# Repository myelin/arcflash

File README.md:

# Arcflash

A board that plugs into all Acorn Archimedes, A3000, A5000 (with adapter), and
Risc PC (with adapter) machines, allowing OS updates without opening the
machine -- or even powering it down!

[Detailed design info](DESIGN.md)

[Stardot thread](https://stardot.org.uk/forums/viewtopic.php?f=16&t=16043)

Pictures
--------

Assembly notes
--------------

For IC sockets, cut two 40-pin headers to make:

- one 2x16-pin header and one 2x4-pin headers
- four 5+4-pin headers and two 2-pin headers

Note from my employer
---------------------

This is not an officially supported Google product. This project is not
eligible for the [Google Open Source Software Vulnerability Rewards
Program](https://bughunters.google.com/open-source-security).

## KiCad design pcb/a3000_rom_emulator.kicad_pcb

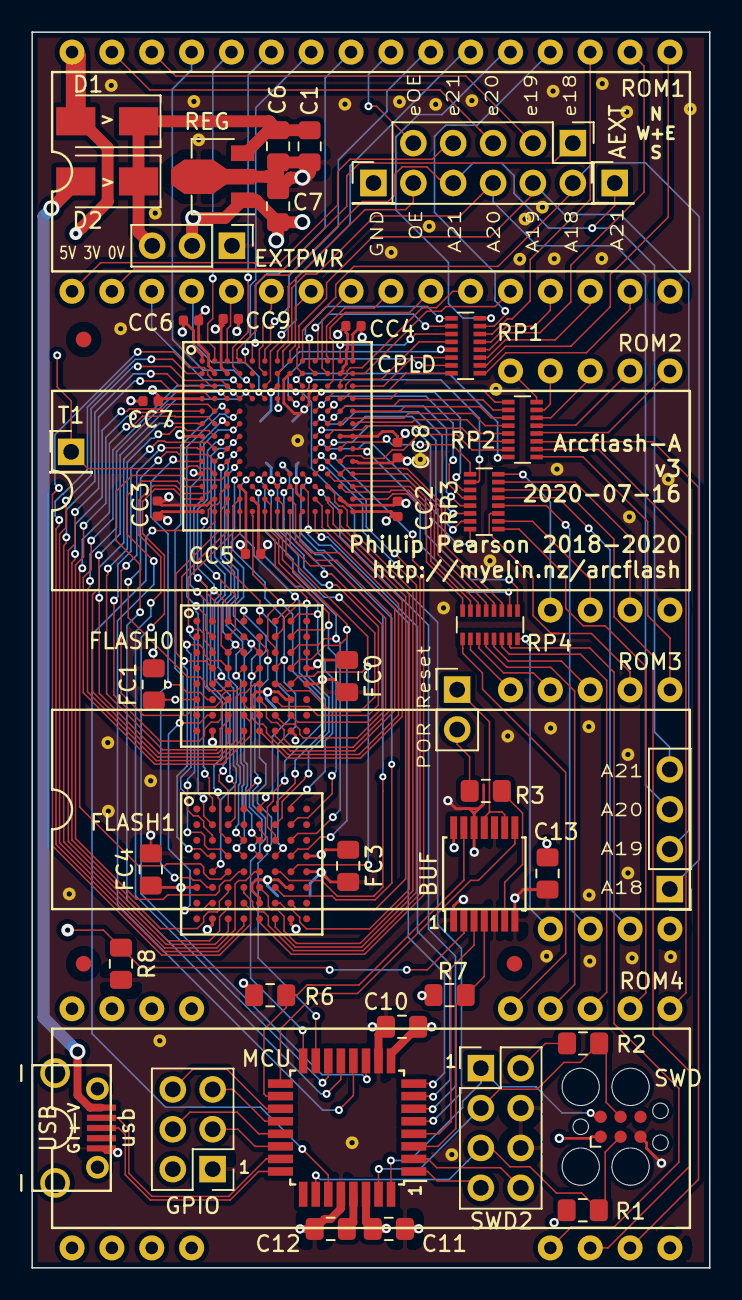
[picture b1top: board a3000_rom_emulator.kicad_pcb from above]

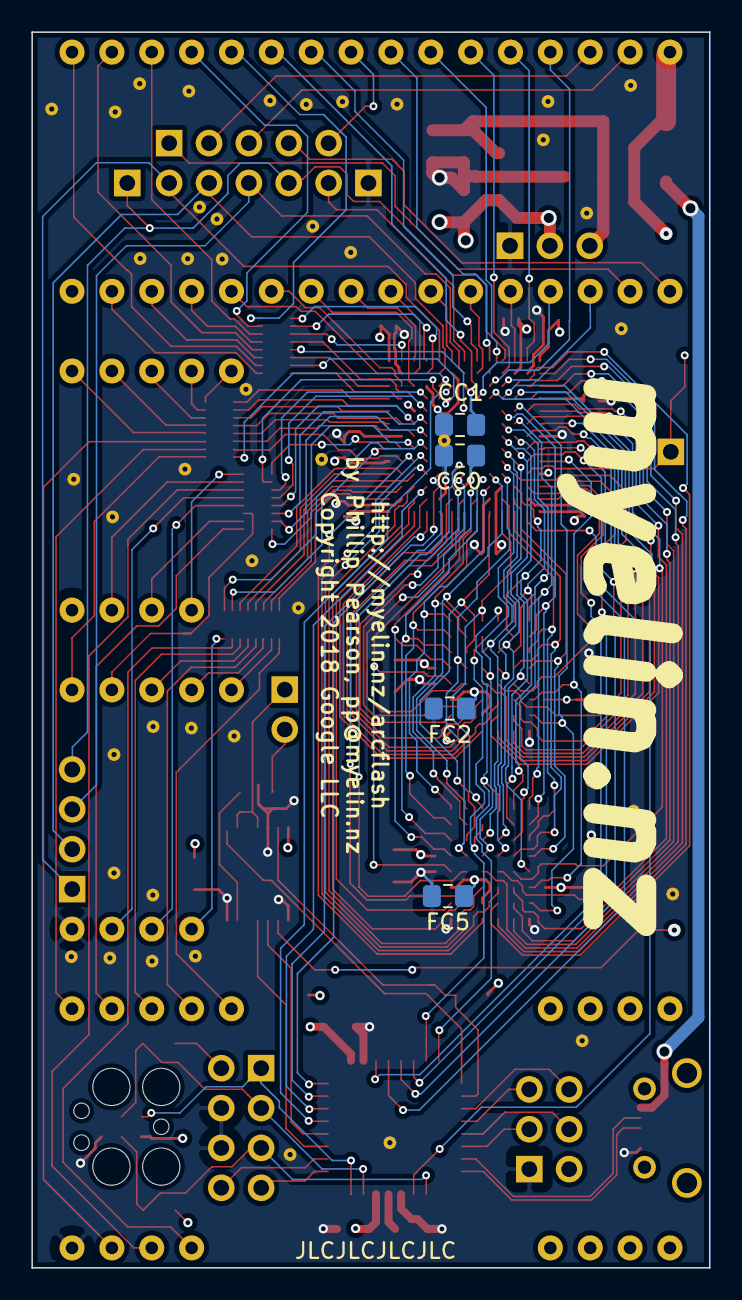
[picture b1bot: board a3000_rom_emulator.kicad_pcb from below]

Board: 4 copper layers, 43.2 x 78.7 mm, 112 parts (4 on the bottom side), 183 nets.

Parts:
A21: rom_A19; PinHeader_1x01_P2.54mm_Vertical
AEXT: Extras; PinHeader_2x05_P2.54mm_Vertical
AEXT2: Addresses; PinHeader_1x04_P2.54mm_Vertical
AEXTGND: Ground; PinHeader_1x01_P2.54mm_Vertical
BUF: 74LVC125PW; TSSOP-14_4.4x5mm_P0.65mm
C1: 10u; C_0805_2012Metric_Pad1.15x1.40mm_HandSolder
C6, C7, C12: 1u; C_0805_2012Metric_Pad1.15x1.40mm_HandSolder
C10, C11, C13: 100n; C_0805_2012Metric_Pad1.15x1.40mm_HandSolder
CC0, CC1: 100n; C_0805_2012Metric_Pad1.15x1.40mm_HandSolder
CC2, CC3, CC4, CC5, CC6, CC7, CC8, CC9: 100n; C_0402_1005Metric
CPLD: XC95144XL-10CSG144; xilinx_csg144
D1: S1ATR; D_SMA
D2: S1ATR NF; D_SMA
EXTPWR: ext pwr; PinHeader_1x03_P2.54mm_Vertical
FC0, FC1, FC2, FC3, FC4, FC5: 100n; C_0805_2012Metric_Pad1.15x1.40mm_HandSolder
FID1, FID2, FID3: FIDUCIAL; Fiducial_1mm_Dia_2mm_Outer
FLASH0, FLASH1: S29GL064S70DHI010; cypress_lae064_fbga
GPIO: gpio; PinHeader_2x03_P2.54mm_Vertical
MCU: ATSAMD21E18A-AU; TQFP-32_7x7mm_P0.8mm
R1, R6, R7, R8: 10k; R_0805_2012Metric_Pad1.15x1.40mm_HandSolder
R2: 1k; R_0805_2012Metric_Pad1.15x1.40mm_HandSolder
R3: 100R; R_0805_2012Metric_Pad1.15x1.40mm_HandSolder
REG: AP7365-33YG-XX; SOT-89-3
RESET: reset/POR; PinHeader_1x02_P2.54mm_Vertical
ROM1: ROM header; dip32_rom
ROM2, ROM3, ROM4: ROM header; dip32_rom_data_only
RP1, RP2, RP3, RP4: Pack of 8 x isolated 68R resistors; R_Array_Convex_8x0602
SWD: swd; Tag-Connect_TC2030-IDC-FP_2x03_P1.27mm_Vertical
SWD2: swd; PinHeader_2x04_P2.54mm_Vertical
T1: rom_5V; PinHeader_1x01_P2.54mm_Vertical
USB: usb; micro_usb_b_smd_molex
mech_pin1, mech_pin2, mech_pin3, mech_pin4, mech_pin5, mech_pin6, mech_pin7, mech_pin8: dip_rom_single_pin
staple_single1, staple_single2, staple_single3, staple_single4, staple_single5, staple_single6, staple_single7, staple_single8, staple_single9, staple_single10, staple_single11, staple_single12, staple_single13, staple_single14, staple_single15, staple_single16, staple_single17, staple_single18, staple_single19, staple_single20, staple_single21, staple_single22, staple_single23, staple_single24, staple_single25, staple_single26, staple_single27, staple_single28, staple_single29, staple_single30, staple_single31, staple_single32, staple_single33, staple_single34, staple_single35, staple_single36, staple_single37, staple_single38, staple_single39, staple_single40, staple_single41, staple_single42, staple_single43, staple_single44, staple_single45: via_single

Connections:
3V3: BUF.14, C7.1, C10.2, C11.2, C13.2, CC0.1, CC1.1, CC2.1, CC3.1, CC4.1, CC5.1, CC6.1, CC7.1, CC8.1, CC9.1, CPLD.A1, CPLD.A13, CPLD.B3, CPLD.C7, CPLD.D1, CPLD.J13, CPLD.L4, CPLD.L7, CPLD.N1, CPLD.N13, EXTPWR.2, FC0.1, FC1.1, FC2.1, FC3.1, FC4.1, FC5.1, FLASH0.D8, FLASH0.F1, FLASH0.F7, FLASH0.G5, FLASH1.D8, FLASH1.F1, FLASH1.F7, FLASH1.G5, GPIO.2, MCU.9, MCU.30, R1.2, R2.2, R6.2, R7.2, REG.1, SWD.1, SWD2.2
5V: C1.2, C6.2, D1.1, D2.1, EXTPWR.3, REG.3
GND: AEXTGND.1, BUF.1, BUF.5, BUF.7, BUF.10, BUF.12, C1.1, C6.1, C7.2, C10.1, C11.1, C12.1, C13.1, CC0.2, CC1.2, CC2.2, CC3.2, CC4.2, CC5.2, CC6.2, CC7.2, CC8.2, CC9.2, CPLD.B2, CPLD.B8, CPLD.B12, CPLD.C10, CPLD.E11, CPLD.G1, CPLD.G12, CPLD.G13, CPLD.K1, CPLD.M2, CPLD.M5, CPLD.M9, CPLD.M12, EXTPWR.1, FC0.2, FC1.2, FC2.2, FC3.2, FC4.2, FC5.2, FLASH0.E8, FLASH0.H2, FLASH0.H7, FLASH1.E8, FLASH1.H2, FLASH1.H7, GPIO.1, MCU.10, MCU.28, R8.2, REG.2, ROM1.16, ROM2.16, ROM3.16, ROM4.16, SWD.5, SWD2.4, SWD2.6, USB.5, staple_single1.1, staple_single2.1, staple_single3.1, staple_single4.1, staple_single5.1, staple_single6.1, staple_single7.1, staple_single8.1, staple_single9.1, staple_single10.1, staple_single11.1, staple_single12.1, staple_single13.1, staple_single14.1, staple_single15.1, staple_single16.1, staple_single17.1, staple_single18.1, staple_single19.1, staple_single20.1, staple_single21.1, staple_single22.1, staple_single23.1, staple_single24.1, staple_single25.1, staple_single26.1, staple_single27.1, staple_single28.1, staple_single29.1, staple_single30.1, staple_single31.1, staple_single32.1, staple_single33.1, staple_single34.1, staple_single35.1, staple_single36.1, staple_single37.1, staple_single38.1, staple_single39.1, staple_single40.1, staple_single41.1, staple_single42.1, staple_single43.1, staple_single44.1, staple_single45.1
USBDM: MCU.23, USB.2
USBDP: MCU.24, USB.3
VDDCORE: C12.2, MCU.29
VUSB: D2.2, USB.1
arc_POR: R3.2, RESET.2
arc_POR_R: BUF.6, R3.1
arc_RESET: BUF.9, BUF.11, RESET.1
arc_RESET_buffered: BUF.8, MCU.17
cpld_MISO: CPLD.L2, MCU.14
cpld_MOSI: CPLD.M1, MCU.11
cpld_SCK: CPLD.L1, MCU.12
cpld_SS: CPLD.K3, MCU.13
cpld_TCK: CPLD.L10, MCU.6
cpld_TDI: CPLD.L9, MCU.8
cpld_TDO: CPLD.C8, MCU.5
cpld_TMS: CPLD.N10, MCU.7
cpld_clock_from_mcu: CPLD.N2, MCU.27
flash0_DQ0: CPLD.J2, FLASH0.E3
flash0_DQ1: CPLD.F1, FLASH0.H3
flash0_DQ2: CPLD.H1, FLASH0.E4
flash0_DQ3: CPLD.D3, FLASH0.H4
flash0_DQ4: CPLD.N11, FLASH0.H5
flash0_DQ5: CPLD.D5, FLASH0.E5
flash0_DQ6: CPLD.N9, FLASH0.H6
flash0_DQ7: CPLD.L6, FLASH0.E6
flash0_DQ8: CPLD.H2, FLASH0.F3
flash0_DQ9: CPLD.G2, FLASH0.G3
flash0_DQ10: CPLD.M10, FLASH0.F4
flash0_DQ11: CPLD.D4, FLASH0.G4
flash0_DQ12: CPLD.M8, FLASH0.F5
flash0_DQ13: CPLD.N8, FLASH0.G6
flash0_DQ14: CPLD.K7, FLASH0.F6
flash0_DQ15: CPLD.L8, FLASH0.G7
flash1_DQ0: CPLD.F2, FLASH1.E3
flash1_DQ1: CPLD.C1, FLASH1.H3
flash1_DQ2: CPLD.E1, FLASH1.E4
flash1_DQ3: CPLD.B1, FLASH1.H4
flash1_DQ4: CPLD.J11, FLASH1.H5
flash1_DQ5: CPLD.C2, FLASH1.E5
flash1_DQ6: CPLD.K10, FLASH1.H6
flash1_DQ7: CPLD.K8, FLASH1.E6
flash1_DQ8: CPLD.E2, FLASH1.F3
flash1_DQ9: CPLD.D2, FLASH1.G3
flash1_DQ10: CPLD.J10, FLASH1.F4
flash1_DQ11: CPLD.C3, FLASH1.G4
flash1_DQ12: CPLD.L11, FLASH1.F5
flash1_DQ13: CPLD.N12, FLASH1.G6
flash1_DQ14: CPLD.K9, FLASH1.F6
flash1_DQ15: CPLD.M11, FLASH1.G7
flash_A0: CPLD.G4, FLASH0.E2, FLASH1.E2
flash_A1: CPLD.M3, FLASH0.D2, FLASH1.D2
flash_A2: CPLD.M4, FLASH0.C2, FLASH1.C2
flash_A3: CPLD.F3, FLASH0.A2, FLASH1.A2
flash_A4: CPLD.E4, FLASH0.B2, FLASH1.B2
flash_A5: CPLD.N3, FLASH0.D3, FLASH1.D3
flash_A6: CPLD.F4, FLASH0.C3, FLASH1.C3
flash_A7: CPLD.G3, FLASH0.A3, FLASH1.A3
flash_A8: CPLD.N6, FLASH0.B6, FLASH1.B6
flash_A9: CPLD.K5, FLASH0.A6, FLASH1.A6
flash_A10: CPLD.N5, FLASH0.C6, FLASH1.C6
flash_A11: CPLD.K4, FLASH0.D6, FLASH1.D6
flash_A12: CPLD.M6, FLASH0.B7, FLASH1.B7
flash_A13: CPLD.L5, FLASH0.A7, FLASH1.A7
flash_A14: CPLD.K6, FLASH0.C7, FLASH1.C7
flash_A15: CPLD.N7, FLASH0.D7, FLASH1.D7
flash_A16: CPLD.M7, FLASH0.E7, FLASH1.E7
flash_A17: CPLD.L3, FLASH0.B3, FLASH1.B3
flash_A18: CPLD.H3, FLASH0.C4, FLASH1.C4
flash_A19: CPLD.J4, FLASH0.D5, FLASH1.D5
flash_A20: CPLD.J3, FLASH0.D4, FLASH1.D4
flash_A21: CPLD.H4, FLASH0.C5, FLASH1.C5
flash_READY: FLASH0.A4, FLASH1.A4, MCU.16
flash_nCE: CPLD.J1, FLASH0.F2, FLASH1.F2
flash_nOE: CPLD.E3, FLASH0.G2, FLASH1.G2
flash_nRESET: FLASH0.B5, FLASH1.B5, MCU.15
flash_nWE: CPLD.N4, FLASH0.A5, FLASH1.A5
mcu_GPIO0: GPIO.3, MCU.22
mcu_GPIO1: GPIO.4, MCU.21
mcu_GPIO2: GPIO.5, MCU.20
mcu_GPIO3: GPIO.6, MCU.19
mcu_RESET: MCU.26, R1.1, SWD.3, SWD2.5
mcu_SWCLK: MCU.31, R2.1, SWD.4, SWD2.3
mcu_SWDIO: MCU.32, SWD.2, SWD2.1
mcu_debug_RXD: MCU.2, SWD2.8
mcu_debug_TXD: MCU.1, SWD2.7
ndrive_arc_POR: BUF.4, MCU.3, R7.1
ndrive_arc_RESET: BUF.13, MCU.18, R6.1
rom_5V: BUF.2, CPLD.K2, D1.2, R8.1, ROM1.32, T1.1
rom_5V_buffered: BUF.3, MCU.4
rom_A0: CPLD.B13, ROM1.12
rom_A1: CPLD.C12, ROM1.11
rom_A2: CPLD.C11, ROM1.10
rom_A3: CPLD.A11, ROM1.9
rom_A4: CPLD.B11, ROM1.8
rom_A5: CPLD.A8, ROM1.7
rom_A6: CPLD.B6, ROM1.6
rom_A7: CPLD.A3, ROM1.5
rom_A8: CPLD.B4, ROM1.27
rom_A9: CPLD.B5, ROM1.26
rom_A10: CPLD.A6, ROM1.23
rom_A11: CPLD.A5, ROM1.25
rom_A12: CPLD.D6, ROM1.4
rom_A13: CPLD.A2, ROM1.28
rom_A14: CPLD.C5, ROM1.29
rom_A15: CPLD.C4, ROM1.3
rom_A16: AEXT.2, AEXT2.1, CPLD.A9
rom_A16_ext: AEXT.1, ROM1.2
rom_A17: AEXT.4, AEXT2.2, CPLD.B9
rom_A17_ext: AEXT.3, ROM1.30
rom_A18: AEXT.6, AEXT2.3, CPLD.B7
rom_A18_ext: AEXT.5, ROM1.31
rom_A19: A21.1, AEXT.8, AEXT2.4, CPLD.A4
rom_A19_ext: AEXT.7, ROM1.1
rom_D0: CPLD.D11, RP1.4
rom_D0_ext: ROM1.13, RP1.13
rom_D1: CPLD.C13, RP1.6
rom_D1_ext: ROM1.14, RP1.11
rom_D2: CPLD.D12, RP1.8
rom_D2_ext: ROM1.15, RP1.9
rom_D3: CPLD.D8, RP1.7
rom_D3_ext: ROM1.17, RP1.10
rom_D4: CPLD.D7, RP1.5
rom_D4_ext: ROM1.18, RP1.12
rom_D5: CPLD.A12, RP1.3
rom_D5_ext: ROM1.19, RP1.14
rom_D6: CPLD.A10, RP1.2
rom_D6_ext: ROM1.20, RP1.15
rom_D7: CPLD.B10, RP1.1
rom_D7_ext: ROM1.21, RP1.16
rom_D8: CPLD.H12, RP3.1
rom_D8_ext: ROM2.13, RP3.16
rom_D9: CPLD.G10, RP3.7
rom_D9_ext: ROM2.14, RP3.10
rom_D10: CPLD.D9, RP3.2
rom_D10_ext: ROM2.15, RP3.15
rom_D11: CPLD.F13, RP2.5
rom_D11_ext: ROM2.17, RP2.12
rom_D12: CPLD.F12, RP2.4
rom_D12_ext: ROM2.18, RP2.13
rom_D13: CPLD.E13, RP2.3
rom_D13_ext: ROM2.19, RP2.14
rom_D14: CPLD.E12, RP2.2
rom_D14_ext: ROM2.20, RP2.15
rom_D15: CPLD.D13, RP2.1
rom_D15_ext: ROM2.21, RP2.16
rom_D16: CPLD.H10, RP4.1
rom_D16_ext: ROM3.13, RP4.16
rom_D17: CPLD.F11, RP3.5
rom_D17_ext: ROM3.14, RP3.12
rom_D18: CPLD.E10, RP3.4
rom_D18_ext: ROM3.15, RP3.13
rom_D19: CPLD.C9, RP2.8
rom_D19_ext: ROM3.17, RP2.9
rom_D20: CPLD.F10, RP3.6
rom_D20_ext: ROM3.18, RP3.11
rom_D21: CPLD.K13, RP4.4
rom_D21_ext: ROM3.19, RP4.13
rom_D22: CPLD.L13, RP4.6
rom_D22_ext: ROM3.20, RP4.11
rom_D23: CPLD.L12, RP4.7
rom_D23_ext: ROM3.21, RP4.10
rom_D24: CPLD.H13, RP4.2
rom_D24_ext: ROM4.13, RP4.15
rom_D25: CPLD.D10, RP3.3
rom_D25_ext: ROM4.14, RP3.14
rom_D26: CPLD.G11, RP2.6
rom_D26_ext: ROM4.15, RP2.11
rom_D27: CPLD.J12, RP2.7
rom_D27_ext: ROM4.17, RP2.10
rom_D28: CPLD.H11, RP3.8
rom_D28_ext: ROM4.18, RP3.9
rom_D29: CPLD.K12, RP4.3
rom_D29_ext: ROM4.19, RP4.14
rom_D30: CPLD.K11, RP4.5
rom_D30_ext: ROM4.20, RP4.12
rom_D31: CPLD.M13, RP4.8
rom_D31_ext: ROM4.21, RP4.9
rom_nCS: CPLD.C6, ROM1.22
rom_nOE: AEXT.10, CPLD.A7
rom_nOE_ext: AEXT.9, ROM1.24

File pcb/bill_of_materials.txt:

Identifier	Value	Description	KiCad package	LCSC part
RP1	Pack of 8 x isolated 68R resistors	8 x 68R pack; https://www.digikey.com/product-detail/en/panasonic-electron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	Resistor_SMD:R_Array_Convex_8x0602	
RP2	Pack of 8 x isolated 68R resistors	8 x 68R pack; https://www.digikey.com/product-detail/en/panasonic-electron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	Resistor_SMD:R_Array_Convex_8x0602	
RP3	Pack of 8 x isolated 68R resistors	8 x 68R pack; https://www.digikey.com/product-detail/en/panasonic-electron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	Resistor_SMD:R_Array_Convex_8x0602	
RP4	Pack of 8 x isolated 68R resistors	8 x 68R pack; https://www.digikey.com/product-detail/en/panasonic-electron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	Resistor_SMD:R_Array_Convex_8x0602	
CC2	100n	Capacitor 0402: 100n	Capacitor_SMD:C_0402_1005Metric	
CC3	100n	Capacitor 0402: 100n	Capacitor_SMD:C_0402_1005Metric	
CC4	100n	Capacitor 0402: 100n	Capacitor_SMD:C_0402_1005Metric	
CC5	100n	Capacitor 0402: 100n	Capacitor_SMD:C_0402_1005Metric	
CC6	100n	Capacitor 0402: 100n	Capacitor_SMD:C_0402_1005Metric	
CC7	100n	Capacitor 0402: 100n	Capacitor_SMD:C_0402_1005Metric	
CC8	100n	Capacitor 0402: 100n	Capacitor_SMD:C_0402_1005Metric	
CC9	100n	Capacitor 0402: 100n	Capacitor_SMD:C_0402_1005Metric	
C10	100n	Capacitor 0805: 100n	Capacitor_SMD:C_0805_2012Metric_Pad1.15x1.40mm_HandSolder	C49678
C11	100n	Capacitor 0805: 100n	Capacitor_SMD:C_0805_2012Metric_Pad1.15x1.40mm_HandSolder	C49678
C13	100n	Capacitor 0805: 100n	Capacitor_SMD:C_0805_2012Metric_Pad1.15x1.40mm_HandSolder	C49678
FC0	100n	Capacitor 0805: 100n	Capacitor_SMD:C_0805_2012Metric_Pad1.15x1.40mm_HandSolder	C49678
FC1	100n	Capacitor 0805: 100n	Capacitor_SMD:C_0805_2012Metric_Pad1.15x1.40mm_HandSolder	C49678
FC3	100n	Capacitor 0805: 100n	Capacitor_SMD:C_0805_2012Metric_Pad1.15x1.40mm_HandSolder	C49678
FC4	100n	Capacitor 0805: 100n	Capacitor_SMD:C_0805_2012Metric_Pad1.15x1.40mm_HandSolder	C49678
CC0	100n NF	Capacitor 0805: 100n NF	Capacitor_SMD:C_0805_2012Metric_Pad1.15x1.40mm_HandSolder	
CC1	100n NF	Capacitor 0805: 100n NF	Capacitor_SMD:C_0805_2012Metric_Pad1.15x1.40mm_HandSolder	
FC2	100n NF	Capacitor 0805: 100n NF	Capacitor_SMD:C_0805_2012Metric_Pad1.15x1.40mm_HandSolder	
FC5	100n NF	Capacitor 0805: 100n NF	Capacitor_SMD:C_0805_2012Metric_Pad1.15x1.40mm_HandSolder	
C1	10u	Capacitor 0805: 10u	Capacitor_SMD:C_0805_2012Metric_Pad1.15x1.40mm_HandSolder	
C6	1u	Capacitor 0805: 1u	Capacitor_SMD:C_0805_2012Metric_Pad1.15x1.40mm_HandSolder	C28323
C7	1u	Capacitor 0805: 1u	Capacitor_SMD:C_0805_2012Metric_Pad1.15x1.40mm_HandSolder	C28323
C12	1u	Capacitor 0805: 1u	Capacitor_SMD:C_0805_2012Metric_Pad1.15x1.40mm_HandSolder	C28323
D1	S1ATR	Diode Rectifier; https://www.digikey.com/products/en?keywords=1655-1502-1-ND	Diode_SMD:D_SMA	
D2	S1ATR NF	Diode Rectifier; https://www.digikey.com/products/en?keywords=1655-1502-1-ND	Diode_SMD:D_SMA	
MCU	ATSAMD21E18A-AU	IC ARM MCU; https://www.digikey.com/products/en?keywords=ATSAMD21E18A-AU-ND	Package_QFP:TQFP-32_7x7mm_P0.8mm	
CPLD	XC95144XL-10CSG144	IC CPLD Xilinx 144MC	myelin-kicad:xilinx_csg144	
REG	AP7365-33YG-XX	IC LDO 3.3V regulator; https://www.digikey.com/products/en?keywords=AP7365-33YG-13DICT-ND	Package_TO_SOT_SMD:SOT-89-3	
BUF	74LVC125PW	IC buffer 4-bit OC LVT; https://www.digikey.com/product-detail/en/74LVT125PW%2c118/1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	Package_SO:TSSOP-14_4.4x5mm_P0.65mm	
FLASH0	S29GL064S70DHI010	IC flash 64Mbit; https://www.digikey.com/products/en?keywords=2015-S29GL064S7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	myelin-kicad:cypress_lae064_fbga	
FLASH1	S29GL064S70DHI010	IC flash 64Mbit; https://www.digikey.com/products/en?keywords=2015-S29GL064S7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	myelin-kicad:cypress_lae064_fbga	
ROM1	ROM header	Pin adapter to emulate a 600mil 32-pin DIP; round pin header strip from Aliexpress	myelin-kicad:dip32_rom	
ROM2	ROM header	Pin adapter to emulate a 600mil 32-pin DIP; round pin header strip from Aliexpress	myelin-kicad:dip32_rom_data_only	
ROM3	ROM header	Pin adapter to emulate a 600mil 32-pin DIP; round pin header strip from Aliexpress	myelin-kicad:dip32_rom_data_only	
ROM4	ROM header	Pin adapter to emulate a 600mil 32-pin DIP; round pin header strip from Aliexpress	myelin-kicad:dip32_rom_data_only	
AEXT2	Addresses	Pin header	Connector_PinHeader_2.54mm:PinHeader_1x04_P2.54mm_Vertical	
AEXT	Extras	Pin header	Connector_PinHeader_2.54mm:PinHeader_2x05_P2.54mm_Vertical	
AEXTGND	Ground	Pin header	Connector_PinHeader_2.54mm:PinHeader_1x01_P2.54mm_Vertical	
T1	rom_5V	Pin header	Connector_PinHeader_2.54mm:PinHeader_1x01_P2.54mm_Vertical	
A21	rom_A19	Pin header	Connector_PinHeader_2.54mm:PinHeader_1x01_P2.54mm_Vertical	
RESET	reset/POR	Pin header - 1x2 0.1 inch male	Connector_PinHeader_2.54mm:PinHeader_1x02_P2.54mm_Vertical	
GPIO	gpio	Pin header NF	Connector_PinHeader_2.54mm:PinHeader_2x03_P2.54mm_Vertical	
SWD2	swd	Pin header NF	Connector_PinHeader_2.54mm:PinHeader_2x04_P2.54mm_Vertical	
EXTPWR	ext pwr	Pin header NF - 1x3 0.1 inch male	Connector_PinHeader_2.54mm:PinHeader_1x03_P2.54mm_Vertical	
R3	100R	Resistor 0805: 100R	Resistor_SMD:R_0805_2012Metric_Pad1.15x1.40mm_HandSolder	
R1	10k	Resistor 0805: 10k	Resistor_SMD:R_0805_2012Metric_Pad1.15x1.40mm_HandSolder	C17414
R6	10k	Resistor 0805: 10k	Resistor_SMD:R_0805_2012Metric_Pad1.15x1.40mm_HandSolder	C17414
R7	10k	Resistor 0805: 10k	Resistor_SMD:R_0805_2012Metric_Pad1.15x1.40mm_HandSolder	C17414
R8	10k	Resistor 0805: 10k	Resistor_SMD:R_0805_2012Metric_Pad1.15x1.40mm_HandSolder	C17414
R2	1k	Resistor 0805: 1k	Resistor_SMD:R_0805_2012Metric_Pad1.15x1.40mm_HandSolder	C17513
USB	usb	Socket Micro USB, Molex 1050170001; https://www.digikey.com/products/en?keywords=WM1399CT-ND	myelin-kicad:micro_usb_b_smd_molex

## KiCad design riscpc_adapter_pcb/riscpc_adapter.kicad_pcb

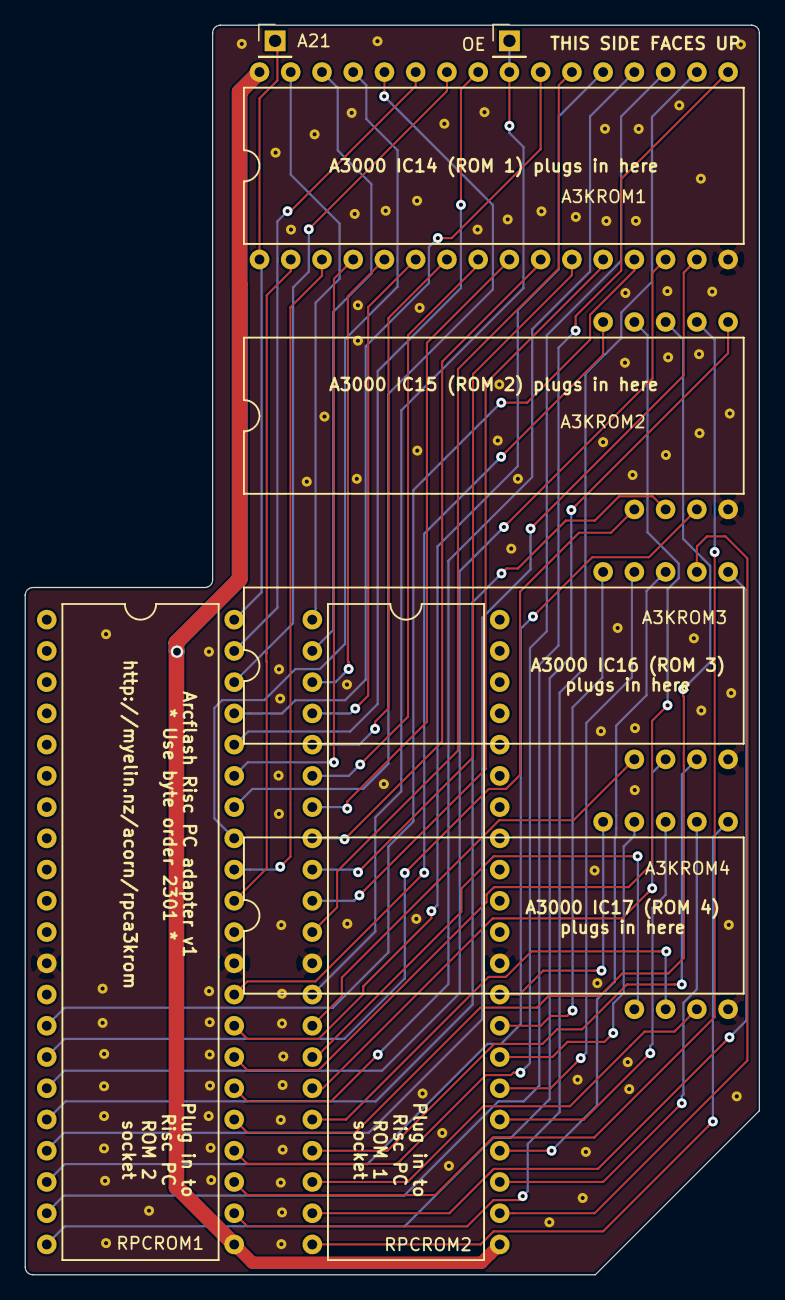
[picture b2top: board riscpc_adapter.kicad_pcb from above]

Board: 2 copper layers, 59.7 x 101.6 mm, 108 parts (0 on the bottom side), 56 nets.

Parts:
A3KROM1: ROM header; dip32_rom
A3KROM2, A3KROM3, A3KROM4: ROM header; dip32_rom_data_only
A21: PinHeader_1x01_P2.54mm_Vertical
OE: PinHeader_1x01_P2.54mm_Vertical
RPCROM1, RPCROM2: ROM header; dip42_rom
staple_single1, staple_single2, staple_single3, staple_single4, staple_single5, staple_single6, staple_single7, staple_single8, staple_single9, staple_single10, staple_single11, staple_single12, staple_single13, staple_single14, staple_single15, staple_single16, staple_single17, staple_single18, staple_single19, staple_single20, staple_single21, staple_single22, staple_single23, staple_single24, staple_single25, staple_single26, staple_single27, staple_single28, staple_single29, staple_single30, staple_single31, staple_single32, staple_single33, staple_single34, staple_single35, staple_single36, staple_single37, staple_single38, staple_single39, staple_single40, staple_single41, staple_single42, staple_single43, staple_single44, staple_single45, staple_single46, staple_single47, staple_single48, staple_single49, staple_single50, staple_single51, staple_single52, staple_single53, staple_single54, staple_single55, staple_single56, staple_single57, staple_single58, staple_single59, staple_single60, staple_single61, staple_single62, staple_single63, staple_single64, staple_single65, staple_single66, staple_single67, staple_single68, staple_single69, staple_single70, staple_single71, staple_single72, staple_single73, staple_single74, staple_single75, staple_single76, staple_single77, staple_single78, staple_single79, staple_single80, staple_single81, staple_single82, staple_single83, staple_single84, staple_single85, staple_single86, staple_single87, staple_single88, staple_single89, staple_single90, staple_single91, staple_single92, staple_single93, staple_single94, staple_single95, staple_single96, staple_single97, staple_single98, staple_single99, staple_single100: via_single

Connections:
5V: A3KROM1.32, RPCROM1.22, RPCROM2.22
A0: A3KROM1.12, RPCROM2.10
A1: A3KROM1.11, RPCROM2.9
A2: A3KROM1.10, RPCROM2.8
A3: A3KROM1.9, RPCROM2.7
A4: A3KROM1.8, RPCROM2.6
A5: A3KROM1.7, RPCROM2.5
A6: A3KROM1.6, RPCROM2.4
A7: A3KROM1.5, RPCROM2.3
A8: A3KROM1.27, RPCROM1.41
A9: A3KROM1.26, RPCROM1.40
A10: A3KROM1.23, RPCROM1.39
A11: A3KROM1.25, RPCROM1.38
A12: A3KROM1.4, RPCROM1.37
A13: A3KROM1.28, RPCROM1.36
A14: A3KROM1.29, RPCROM1.35
A15: A3KROM1.3, RPCROM1.34
A16: A3KROM1.2, RPCROM1.33
A17: A3KROM1.30, RPCROM2.2
A18: A3KROM1.31, RPCROM2.1
A19: A3KROM1.1, A21.1, RPCROM1.42
D0: A3KROM1.13, RPCROM1.14
D1: A3KROM1.14, RPCROM1.16
D2: A3KROM1.15, RPCROM1.18
D3: A3KROM1.17, RPCROM1.20
D4: A3KROM1.18, RPCROM1.23
D5: A3KROM1.19, RPCROM1.25
D6: A3KROM1.20, RPCROM1.27
D7: A3KROM1.21, RPCROM1.29
D8: A3KROM2.13, RPCROM1.15
D9: A3KROM2.14, RPCROM1.17
D10: A3KROM2.15, RPCROM1.19
D11: A3KROM2.17, RPCROM1.21
D12: A3KROM2.18, RPCROM1.24
D13: A3KROM2.19, RPCROM1.26
D14: A3KROM2.20, RPCROM1.28
D15: A3KROM2.21, RPCROM1.30
D16: A3KROM3.13, RPCROM2.14
D17: A3KROM3.14, RPCROM2.16
D18: A3KROM3.15, RPCROM2.18
D19: A3KROM3.17, RPCROM2.20
D20: A3KROM3.18, RPCROM2.23
D21: A3KROM3.19, RPCROM2.25
D22: A3KROM3.20, RPCROM2.27
D23: A3KROM3.21, RPCROM2.29
D24: A3KROM4.13, RPCROM2.15
D25: A3KROM4.14, RPCROM2.17
D26: A3KROM4.15, RPCROM2.19
D27: A3KROM4.17, RPCROM2.21
D28: A3KROM4.18, RPCROM2.24
D29: A3KROM4.19, RPCROM2.26
D30: A3KROM4.20, RPCROM2.28
D31: A3KROM4.21, RPCROM2.30
GND: A3KROM1.16, A3KROM2.16, A3KROM3.16, A3KROM4.16, RPCROM1.12, RPCROM1.31, RPCROM2.12, RPCROM2.31, staple_single1.1, staple_single2.1, staple_single3.1, staple_single4.1, staple_single5.1, staple_single6.1, staple_single7.1, staple_single8.1, staple_single9.1, staple_single10.1, staple_single11.1, staple_single12.1, staple_single13.1, staple_single14.1, staple_single15.1, staple_single16.1, staple_single17.1, staple_single18.1, staple_single19.1, staple_single20.1, staple_single21.1, staple_single22.1, staple_single23.1, staple_single24.1, staple_single25.1, staple_single26.1, staple_single27.1, staple_single28.1, staple_single29.1, staple_single30.1, staple_single31.1, staple_single32.1, staple_single33.1, staple_single34.1, staple_single35.1, staple_single36.1, staple_single37.1, staple_single38.1, staple_single39.1, staple_single40.1, staple_single41.1, staple_single42.1, staple_single43.1, staple_single44.1, staple_single45.1, staple_single46.1, staple_single47.1, staple_single48.1, staple_single49.1, staple_single50.1, staple_single51.1, staple_single52.1, staple_single53.1, staple_single54.1, staple_single55.1, staple_single56.1, staple_single57.1, staple_single58.1, staple_single59.1, staple_single60.1, staple_single61.1, staple_single62.1, staple_single63.1, staple_single64.1, staple_single65.1, staple_single66.1, staple_single67.1, staple_single68.1, staple_single69.1, staple_single70.1, staple_single71.1, staple_single72.1, staple_single73.1, staple_single74.1, staple_single75.1, staple_single76.1, staple_single77.1, staple_single78.1, staple_single79.1, staple_single80.1, staple_single81.1, staple_single82.1, staple_single83.1, staple_single84.1, staple_single85.1, staple_single86.1, staple_single87.1, staple_single88.1, staple_single89.1, staple_single90.1, staple_single91.1, staple_single92.1, staple_single93.1, staple_single94.1, staple_single95.1, staple_single96.1, staple_single97.1, staple_single98.1, staple_single99.1, staple_single100.1
nCS: A3KROM1.22, RPCROM2.11
nOE: A3KROM1.24, OE.1, RPCROM2.13

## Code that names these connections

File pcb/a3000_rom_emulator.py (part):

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
# done(v2) verify 74lvt125 pinout

# done(v2) add nOE pulldown or nearby ground pin for A3xx compatibility
# done(v2) update jumper silkscreen to make docs easier to write
# let's do it like this:
#     eOE e21 e20 e19 e18
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#     pins=[
#         Pin(1, "STANDBY#",  "3V3"),
#         Pin(2, "GND",       "GND"),
#         Pin(3, "OUT",       "cpld_clock_osc"),  # this used to connect to K2 on the CPLD (now used to detect rom_5V / host power)
#         Pin(4, "VDD",       "3V3"),
#     ],
# )
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        # == 117
        # MCU can drive flash_nRESET and read flash_READY
        Pin( "A1", "VCCIO",    "3V3"),
        Pin( "A2", "",         "rom_A13"),
        Pin( "A3", "",         "rom_A7"),
        Pin( "A4", "",         "rom_A19"),
        Pin( "A5", "",         "rom_A11"),
        Pin( "A6", "",         "rom_A10"),
        Pin( "A7", "",         "rom_nOE"),
        Pin( "A8", "",         "rom_A5"),
        Pin( "A9", "",         "rom_A16"),
        Pin("A10", "",         "rom_D6"),
        Pin("A11", "",         "rom_A3"),
        Pin("A12", "",         "rom_D5"),
        Pin("A13", "VCCIO",    "3V3"),
        Pin( "B1", "",         "flash1_DQ3"),
        Pin( "B2", "GND",      "GND"),
        Pin( "B3", "VCCINT",   "3V3"),
        Pin( "B4", "",         "rom_A8"),
        Pin( "B5", "",         "rom_A9"),
        Pin( "B6", "",         "rom_A6"),
        Pin( "B7", "",         "rom_A18"),
        Pin( "B8", "GND",      "GND"),
        Pin( "B9", "",         "rom_A17"),
        Pin("B10", "",         "rom_D7"),
        Pin("B11", "",         "rom_A4"),
        Pin("B12", "GND",      "GND"),
        Pin("B13", "",         "rom_A0"),
        Pin( "C1", "",         "flash1_DQ1"),
        Pin( "C2", "",         "flash1_DQ5"),
        Pin( "C3", "",         "flash1_DQ11"),
        Pin( "C4", "",         "rom_A15"),
        Pin( "C5", "",         "rom_A14"),
        Pin( "C6", "",         "rom_nCS"),
        Pin( "C7", "VCCIO",    "3V3"),
        Pin( "C8", "TDO",      "cpld_TDO"),
        Pin( "C9", "",         "rom_D19"),
        Pin("C10", "GND",      "GND"),
        Pin("C11", "",         "rom_A2"),
        Pin("C12", "",         "rom_A1"),
        Pin("C13", "",         "rom_D1"),
        Pin( "D1", "VCCINT",   "3V3"),
        Pin( "D2", "",         "flash1_DQ9"),
        Pin( "D3", "",         "flash0_DQ3"),
        Pin( "D4", "",         "flash0_DQ11"),
        Pin( "D5", "",         "flash0_DQ5"),
        Pin( "D6", "",         "rom_A12"),
        Pin( "D7", "",         "rom_D4"),
        Pin( "D8", "",         "rom_D3"),
        Pin( "D9", "",         "rom_D10"),
        Pin("D10", "",         "rom_D25"),
        Pin("D11", "",         "rom_D0"),
        Pin("D12", "",         "rom_D2"),
        Pin("D13", "",         "rom_D15"),

        Pin( "E1", "",         "flash1_DQ2"),
        Pin( "E2", "",         "flash1_DQ8"),
        Pin( "E3", "",         "flash_nOE"),
        Pin( "E4", "",         "flash_A4"),
        Pin("E10", "",         "rom_D18"),
        Pin("E11", "GND",      "GND"),
        Pin("E12", "",         "rom_D14"),
        Pin("E13", "",         "rom_D13"),
        Pin( "F1", "",         "flash0_DQ1"),
        Pin( "F2", "",         "flash1_DQ0"),
        Pin( "F3", "",         "flash_A3"),
        Pin( "F4", "",         "flash_A6"),
        Pin("F10", "",         "rom_D20"),
        Pin("F11", "",         "rom_D17"),
        Pin("F12", "",         "rom_D12"),
        Pin("F13", "",         "rom_D11"),
        Pin( "G1", "GND",      "GND"),
        Pin( "G2", "",         "flash0_DQ9"),
        Pin( "G3", "",         "flash_A7"),
        Pin( "G4", "",         "flash_A0"),
        Pin("G10", "",         "rom_D9"),
        Pin("G11", "",         "rom_D26"),
        Pin("G12", "GND",      "GND"),
        Pin("G13", "GND",      "GND"),
        Pin( "H1", "",         "flash0_DQ2"),
        Pin( "H2", "",         "flash0_DQ8"),
        Pin( "H3", "",         "flash_A18"),
        Pin( "H4", "",         "flash_A21"),
        Pin("H10", "",         "rom_D16"),
        Pin("H11", "",         "rom_D28"),
        Pin("H12", "",         "rom_D8"),
        Pin("H13", "",         "rom_D24"),
        Pin( "J1", "",         "flash_nCE"),
        Pin( "J2", "",         "flash0_DQ0"),
        Pin( "J3", "",         "flash_A20"),
        Pin( "J4", "",         "flash_A19"),
        Pin("J10", "",         "flash1_DQ10"),
        Pin("J11", "",         "flash1_DQ4"),
        Pin("J12", "",         "rom_D27"),
        Pin("J13", "VCCINT",   "3V3"),

        Pin( "K1", "GND",      "GND"),
        Pin( "K2", "GCK1",     "rom_5V"),
        Pin( "K3", "",         "cpld_SS"),
        Pin( "K4", "",         "flash_A11"),
        Pin( "K5", "",         "flash_A9"),
        Pin( "K6", "",         "flash_A14"),
        Pin( "K7", "",         "flash0_DQ14"),
        Pin( "K8", "",         "flash1_DQ7"),
        Pin( "K9", "",         "flash1_DQ14"),
        Pin("K10", "",         "flash1_DQ6"),
        Pin("K11", "",         "rom_D30"),
        Pin("K12", "",         "rom_D29"),
        Pin("K13", "",         "rom_D21"),
        Pin( "L1", "GCK2",     "cpld_SCK"),
        Pin( "L2", "",         "cpld_MISO"),
        Pin( "L3", "",         "flash_A17"),
        Pin( "L4", "VCCINT",   "3V3"),
        Pin( "L5", "",         "flash_A13"),
        Pin( "L6", "",         "flash0_DQ7"),
        Pin( "L7", "VCCIO",    "3V3"),
        Pin( "L8", "",         "flash0_DQ15"),
        Pin( "L9", "TDI",      "cpld_TDI"),
        Pin("L10", "TCK",      "cpld_TCK"),
        Pin("L11", "",         "flash1_DQ12"),
        Pin("L12", "",         "rom_D23"),
        Pin("L13", "",         "rom_D22"),
        Pin( "M1", "",         "cpld_MOSI"),
        Pin( "M2", "GND",      "GND"),
        Pin( "M3", "",         "flash_A1"),
        Pin( "M4", "",         "flash_A2"),
        Pin( "M5", "GND",      "GND"),
        Pin( "M6", "",         "flash_A12"),
        Pin( "M7", "",         "flash_A16"),
        Pin( "M8", "",         "flash0_DQ12"),
        Pin( "M9", "GND",      "GND"),
        Pin("M10", "",         "flash0_DQ10"),
        Pin("M11", "",         "flash1_DQ15"),
        Pin("M12", "GND",      "GND"),
        Pin("M13", "",         "rom_D31"),
        Pin( "N1", "VCCIO",    "3V3"),
        Pin( "N2", "GCK3",     "cpld_clock_from_mcu"),
        Pin( "N3", "",         "flash_A5"),
        Pin( "N4", "",         "flash_nWE"),
        Pin( "N5", "",         "flash_A10"),
        Pin( "N6", "",         "flash_A8"),
        Pin( "N7", "",         "flash_A15"),
        Pin( "N8", "",         "flash0_DQ13"),
        Pin( "N9", "",         "flash0_DQ6"),
        Pin("N10", "TMS",      "cpld_TMS"),
        Pin("N11", "",         "flash0_DQ4"),
        Pin("N12", "",         "flash1_DQ13"),
        Pin("N13", "VCCIO",    "3V3"),
    ],
)
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        desc="Diode Rectifier; https://www.digikey.com/products/en?keywords=1655-1502-1-ND",
        pins=[
            Pin(1, "1", "5V"),
            Pin(2, "2", "rom_5V"),
        ],
    ),
    myelin_kicad_pcb.Component(
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        desc="Diode Rectifier; https://www.digikey.com/products/en?keywords=1655-1502-1-ND",
        pins=[
            Pin(1, "1", "5V"),
            Pin(2, "2", "VUSB"),
        ],
    ),
]
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        buses=[""],
        pins=[
            Pin("F1", "Vio",     "3V3"),
            Pin("A2", "A3",      "flash_A3"),
            Pin("B2", "A4",      "flash_A4"),
            Pin("C2", "A2",      "flash_A2"),
            Pin("D2", "A1",      "flash_A1"),
            Pin("E2", "A0",      "flash_A0"),
            Pin("F2", "CE#",     "flash_nCE"),
            Pin("G2", "OE#",     "flash_nOE"),
            Pin("H2", "VSS",     "GND"),
            Pin("A3", "A7",      "flash_A7"),
            Pin("B3", "A17",     "flash_A17"),
            Pin("C3", "A6",      "flash_A6"),
            Pin("D3", "A5",      "flash_A5"),
            Pin("E3", "DQ0",     "flash%d_DQ0" % flash_id),
            Pin("F3", "DQ8",     "flash%d_DQ8" % flash_id),
            Pin("G3", "DQ9",     "flash%d_DQ9" % flash_id),
            Pin("H3", "DQ1",     "flash%d_DQ1" % flash_id),
            Pin("A4", "RY/BY#",  "flash_READY"),
            Pin("B4", "WP#/ACC"),  # contains an internal pull-up so we can leave it NC
            Pin("C4", "A18",     "flash_A18"),
            Pin("D4", "A20",     "flash_A20"),
            Pin("E4", "DQ2",     "flash%d_DQ2" % flash_id),
            Pin("F4", "DQ10",    "flash%d_DQ10" % flash_id),
            Pin("G4", "DQ11",    "flash%d_DQ11" % flash_id),
            Pin("H4", "DQ3",     "flash%d_DQ3" % flash_id),
            Pin("A5", "WE#",     "flash_nWE"),
            Pin("B5", "RESET#",  "flash_nRESET"),
            Pin("C5", "A21",     "flash_A21"),
            Pin("D5", "A19",     "flash_A19"),
            Pin("E5", "DQ5",     "flash%d_DQ5" % flash_id),
            Pin("F5", "DQ12",    "flash%d_DQ12" % flash_id),
            Pin("G5", "Vcc",     "3V3"),
            Pin("H5", "DQ4",     "flash%d_DQ4" % flash_id),
            Pin("A6", "A9",      "flash_A9"),
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
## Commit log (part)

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2017-04-21 Initial import
2017-05-01 Finished 32kb_flash_cartridge mini and standard board layouts
2017-05-03 Added third_party/libxsvf (ISC license) submodule
2017-10-31 atsamd11_pro_micro: little tester board for the ATSAMD11C14
2017-10-31 Fixed up drill file building -- it doesn't appear to work until the plotter has been closed
2017-10-31 Cherry MX keyswitch footprint tester
2017-11-01 Add pcb-tools, required by preview generator
2017-11-02 Forgot to add this: initial setup script
2017-11-10 Fixed path to atsamd21_usb_host
2017-11-12 'make' now just builds everything, rather than rebuilding everything
2017-11-15 econet_hub: Socket box + clock + termination for a small Econet network
2017-11-19 Make the default text size a bit smaller
2017-11-23 fx2_tube_cartridge_adapter: Started on PCB
2017-12-07 rom_socket_level_shifter: DRC passes, board probably works, but looks extremely ugly
2017-12-07 Build netlists before fab files
2018-04-28 Update to new Arduino-Makefile version
2018-06-05 Various updates to master_updateable_megarom: SCK reliability experiments, and mods to run in a Model B
2018-06-05 .gitignore update
2018-11-22 a3000_rom_emulator: draft daisychain routing of the flash chips done
2018-11-24 Fixed hole sizes in sockets, and removed flash2-5
2018-12-04 CPLD partially routed
2018-12-06 Added pics
2018-12-07 Silkscreen, some tracks
2018-12-11 Added some more staples
2018-12-17 Added pullup on A21, for predictable results when it's not wired to the motherboard
2018-12-17 tidied some silkscreen and regenerated renders
2018-12-19 Updated RAM connector per cmorley's advice on Stardot: moved the left block of 20 pins 25 mils right
2018-12-21 arcflash ready for fab, I think
2018-12-21 Sync latest footprints
2018-12-28 Generated position files for v1, including fiducials (which needed to be changed from virtual to smd placement type to show up in the .pos files)
2018-12-28 Set smd attribute on parts that weren't showing up in the pos files
2019-01-03 First successful CPLD build
2019-01-03 update libxsvf to program xc95144xl chip on a3000_rom_emulator
2019-01-04 Ported programming algorithm from megarom code
2019-01-05 Switch to readBytes for better serial performance
2019-01-05 Benchmarking and debugging, and made chip_size() return total bytes on the board rather than for one chip
2019-01-07 A5000 adapter board for Arcflash project
2019-01-08 start of assembly routines -- simple one just to reset system
2019-01-10 Attempting to create a new A3000 test ROM, built using modern tools
2019-01-11 Progress: the program now links, and appears to run OK in Arculator. One big glitch was that I didn't have .rodata in the text segment, and it was getting copied into .data, so my program was using t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
2019-01-14 Fix Python 3 issues
2019-01-19 Tracking Romcs* pulse and detecting when our signal words are being read
2019-01-20 SPI maxes out at 12MHz
2019-01-24 Startup mostly works -- doesn't correctly set up A3000 from cold boot, but runs in Arculator and starts if switched to after RO3 has already booted
2019-01-28 Text display works on pre-memory startup. Added start of BCD conversion, so we can print numbers too.
2019-01-29 Detect memory size and set MEMC block size. Works in Arculator.
2019-01-29 Successfully copying RXD to TXD at 9600 bps
2019-02-01 Bit banged serial port works for transmission; reception code is there but untested
2019-02-03 Untested code to read CMOS settings
2019-02-06 Tidied silkscreen and edges, and brought bottom right edge in a bit
2019-02-07 More messing around with traces on riscpc adapter board
2019-02-08 a whole lot more staples
2019-02-08 v1, ready to go to JLC
2019-02-11 text display works in C now too. starting on keyboard routines.
2019-02-11 Initializing keyboard and reading mouse
2019-02-12 Realized I can skip all the << 16 stuff by just making all IOC regs uint8_t*. More attempts to make keyboard init properly.
2019-02-12 Flash bank selection now works -- hit 0-7 then reset on the A3000, and you're in the new OS!
2019-02-17 Starting on v2: renamed arc_RESET pin to rom_nOE and added jumper to connect LA21 to rom_A19
2019-02-17 Added 1 and > graphics to make assembly easier
2019-02-19 Switch stb_sprintf over to 32-bit integers so we don't need __aeabi_uldivmod, and make everything use display_printf rather than many display_print_* calls.
2019-02-19 Starting to use protos for bank and cmos storage (and comms in future)
2019-03-03 Another .ramfunc function; considering just moving everything into that section...
2019-03-04 python lib now generates proper flash images, and bootloader can now read protos
2019-03-06 New menu system seems to work
2019-03-06 Made kb/mouse debug info not mess up display
2019-03-07 Now executing everything from RAM, and properly clearing the screen on boot so we don't need to clear it a second time in main()
2019-04-22 Handling byte_order argument to FlashImage, to support Risc PC / A5000 adapters
2019-04-28 remove conditional display of IOMD in banner, because IOMD bootloader doesn't use start.s at all
2019-04-28 Fix bug with padding -- it was only showing up when I had three 4MB images
2019-04-28 Latest component footprints
2019-05-04 Include bootloader.bin in PyPI package
2019-05-16 Arc keyboard USB interface
2019-06-12 Arcflash-A v2 final; from a couple of weeks ago
2019-08-13 renamed rom_emulator.ino so the firmware is buildable with the Arduino IDE
2019-09-08 Arcflash: initial v2 firmware support; moved libxsvf from libraries to src, to experiment with building under the Arduino IDE.
2019-09-08 Arcflash: change serial detection order so as to not get confused by a particular USB-serial adapter I have plugged in often
2019-09-13 Successfully detecting RESET double-clicks, and resetting machine when OS selected in bootloader
2019-09-14 Now always doing a power on reset into a selected OS (also POR works!)
2019-11-17 MGC MKII: Disabled shift register while debugging bitbang; rom/ram select and eeprom lock/unlock work now, but SD doesn't.
2020-05-16 Allow remote server to be specified for Xilinx builds with REMOTE_HOST arg. Do remote Xilinx builds in a spcified parent dir rather than filling the remote home dir.
2020-07-17 arcflash: v3 PCB with 68R resistor packs to provide some protection/damping to data lines
2020-07-25 arcflash: Python 3 support, bootloader build script update, notes in bootloader asm
2020-07-25 arcflash: Only respond on comms interface for top 4 words, not 8 words, of ROM
2020-07-25 arcflash: Add an option to sync SPI signals to the 48MHz clock (fitting fails with this enabled)
2021-01-17 arcflash: Clarify that bottom-layer decoupling capacitors are optional
2021-01-19 arcflash: Switch build process over to using arduino-cli
2021-01-20 arcflash: Make our own Arduino variant so Arcflash boards show up as Arcflash rather than Circuit Playground Express USB devices
2021-01-20 arcflash: Document tools dir
2021-01-20 arcflash: Simplify bootloader rebuild process
2021-01-25 arcflash: Update URLs to use new GitHub main branch
2021-01-26 Switch .gitmodules from git@github.com to https://github.com urls, so works without a GH login
2021-03-06 arcflash: Switch over to adafruit/ArduinoCore-samd, and copy the most important bits into third_party/myelin-arduino-hardware.
2021-03-16 arcflash: based on adafruit:samd rather than arduino:samd now
2021-07-19 post_box_usb: Start r4; generate JLCPCB BOM so I can get them to assemble these.
2025-01-14 arcflash: Added skeleton of new testbench, using cocotb
2025-01-31 Add not-an-official-Google-project note to README.md
2025-01-31 Add copyright headers to files where necessary.
2025-02-03 Update relative paths to work without a3000_rom_emulator top level dir
2025-02-04 Include correct copyright line in third_party/arm-trusted-firmware/LICENSE
2025-03-08 cpld: Add test for writing a word to the flash chips
2025-03-10 cpld: Add option to disable the serial port, and tests for serial port reads and writes.
2025-03-15 cpld: Add local build script, and CPLD programming tool.
2025-03-17 firmware: Use bool for bitbang_serial_have_star variable
2025-03-17 firmware: Disable serial port after selecting an OS to boot
2025-03-17 Fix up more paths to work with the new repo layout
2025-03-18 firmware: send OK in response to unknown chars, so ROM uploads don't get stuck at first
2025-03-18 os_switcher_bootloader: Update URL to use https
2025-03-18 python_lib: Convert to pyproject.toml
2025-03-18 os_switcher_bootloader: Display build date in title
2025-03-19 firmware: Make cached build the default Makefile target
2025-03-19 os_switcher_bootloader: Always rebuild main.cc to update version
2025-03-19 third_party/crc32: Add https://github.com/stbrumme/crc32
2025-03-20 Update top level Makefile to only build Arcflash targets
2025-03-20 firmware: Completely replace lib folders if we're doing a clean build
2025-03-20 os_switcher_bootloader: Explain the different bootloader targets
2025-03-21 Fix bit-bang serial reception.
    The missing IOC_TIMER1_GO line in read_serial_byte() was causing the
    incoming bits to be sampled right as they were changing, which was
    extremely unreliable.
2025-03-22 Top level Makefile: Run host_mcu_comms tests
2025-03-23 cpld: Improve test names and function comments
2025-03-23 cpld: Add test for bank switching and ARM flash reads
2025-03-24 cpld: Byte-align control, address, and data in SPI transactions
    (In the hope that this simplifies the synthesized logic.)
2025-03-26 python_lib: 'arcflash upload' command, to upload a prebuilt flash image.
2025-03-26 python_lib: Include BOSSA license.
2025-03-26 python_lib: Moved _bossa.cc out into third_party, seeing as it's based on BOSSA code.
2025-03-27 python_lib: Remove afserial.py, which is obsoleted by port.py
2025-03-27 Makefiles: Top-level 'make' now runs tests and does an incremental build
2025-03-27 python_lib: Make symlinks so GitHub Python build won't fail with directory traversal errors
2025-03-27 .github: Checkout submodules
2025-03-27 .github: Disable Windows and musllinux builds
2025-03-28 third_party/bossa_wrapper: Use portable time functions in _bossa.cc
2025-03-28 python_lib: Build correct sources on macOS, Linux, Windows.
2025-03-29 python_lib: Add basic smoke test
2025-03-29 firmware: Update built firmware
2025-04-01 Move descriptor size word to 896KiB (0xe0000), followed by descriptor (0xe0004)
2025-04-01 python_lib: Add built firmware, make 'arcflash program-mcu' program packaged version
2025-04-01 python_lib: Add CPLD SVF, make 'arcflash program-cpld' program packaged version
2025-04-03 python_lib: Pin to protobuf 5.x, to match the libprotoc version used for compilation
2025-04-03 .github: Add workflow to run host_mcu_comms tests
2025-04-04 pcb: Update to KiCad 9, fix Makefile to build fab outputs again
2025-04-05 Create workflow to build and publish arcflash-builder Docker image
2025-04-06 Fix container name
2025-04-06 Install git in Docker image
2025-04-06 Try again -- it didn't pick up the new Docker image
2025-04-06 One more time...
2025-04-06 Make 'make -C nanopb/generator/proto clean' work
2025-04-06 Don't call the arcflash script from 'make release', so it works under GitHub Actions
2025-04-07 build(deps): bump actions/download-artifact in /.github/workflows
    Bumps [actions/download-artifact](https://github.com/actions/download-artifact) from 4.1.1 to 4.1.3.
    - [Release notes](https://github.com/actions/download-artifact/releases)
    - [Commits](https://github.com/actions/download-artifact/compare/v4.1.1...v4.1.3)
    ---
    updated-dependencies:
    - dependency-name: actions/download-artifact
2025-04-07 docker: Update Arduino core index using arduino-cli.yaml
2025-04-07 os_switcher_bootloader: Use tag name from GitHub, or short git ref, as version
2025-04-07 firmware: Add version.h
2025-04-09 .github: Consolidate all workflows, to properly trigger Python build.
2025-04-09 Limit Docker builds to main branch
2025-04-09 os_switcher_bootloader: Build under -Wall -Werror, correctly align version in screen header
2025-04-09 Remove built binaries that are now generated in the GitHub build workflow

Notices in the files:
pcb/a3000_rom_emulator.py:
Copyright 2018 Google Inc.
Licensed under the Apache License, Version 2.0 (the "License");
pcb/a3000_rom_emulator.kicad_pcb:
Copyright 2018 Google LLC
